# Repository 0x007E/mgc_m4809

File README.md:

# `MGC_module` - ATmega4809

The `ATmega4809` (`mgc_module`) is an adaptable board for the [MeGARCard](https://github.com/0x007e/mgc). The board offers the possibility to control the `MeGARCard` with an [ATmega4809](#additional-information). The board itself is connected to the `MeGARCard` within the pcb-to-pcb connectors (no soldering necessary). With the onboard dip-switches the board voltage can be regulated from `3V3` to `5V`. Also the usage of hardware-/software-`twi` to control the [SSD1306](#additional-information)-display on the megacard can be selected.

> To mount the board on the `MeGARCard` disconnect the power source (`USB-C` connector) or any other used source from the MeGARCard!

| Experience  | Level                                                                               |
|:------------|:-----------------------------------------------------------------------------------:|
| Soldering   |  |

# Downloads

| Type      | File                                                                                                                                                 | Description     |
|:---------:|:----------------------------------------------------------------------------------------------------------------------------------------------------:|:----------------|
| Schematic | [pdf](https://github.com/0x007E/mgc_m4809/releases/latest/download/schematic.pdf) / [cadlab](https://cadlab.io/project/30419/main/files)                   | Schematic files |
| Board     | [pdf](https://github.com/0x007E/mgc_m4809/releases/latest/download/pcb.pdf) / [cadlab](https://cadlab.io/project/30419/main/files)                         | Board file      |
| Drill     | [pdf](https://github.com/0x007E/mgc_m4809/releases/latest/download/drill.pdf)                                                                              | Drill file      |
| BoM | [xlsx](https://github.com/0x007E/mgc_m4809/releases/latest/download/bom.xlsx) / [html](https://github.com/0x007E/mgc_m4809/releases/latest/download/ibom.html)          | Bill of Material as Excel/interactive HTML |
| PCB    | [zip](https://github.com/0x007E/mgc_m4809/releases/latest/download/kicad.zip) / [tar](https://github.com/0x007E/mgc_m4809/releases/latest/download/kicad.tar.gz)    | KiCAD/Gerber/BoM/Drill files       |

# Hardware

The pcb is created with `KiCAD`. All files are built with `github actions` so that they are ready for a production environment.

## PCB

The circuit board is populated on both sides (Top, Bottom). The best way for soldering the `SMD` components is within a vapor phase soldering system and for the `THT` components with a standard soldering system.

### Top Layer

### Bottom Layer

# Additional Information

| Type       | Link               | Description              |
|:----------:|:------------------:|:-------------------------|
| ATmega4809  | [pdf](https://ww1.microchip.com/downloads/en/DeviceDoc/ATmega4808-4809-Data-Sheet-DS40002173A.pdf) | ATmega4808/4809 Data Sheet |
| SSD1306 | [pdf](https://www.vishay.com/docs/37902/oled128o064dbpp3n00000.pdf) | 128 x 64 Graphic OLED |

---

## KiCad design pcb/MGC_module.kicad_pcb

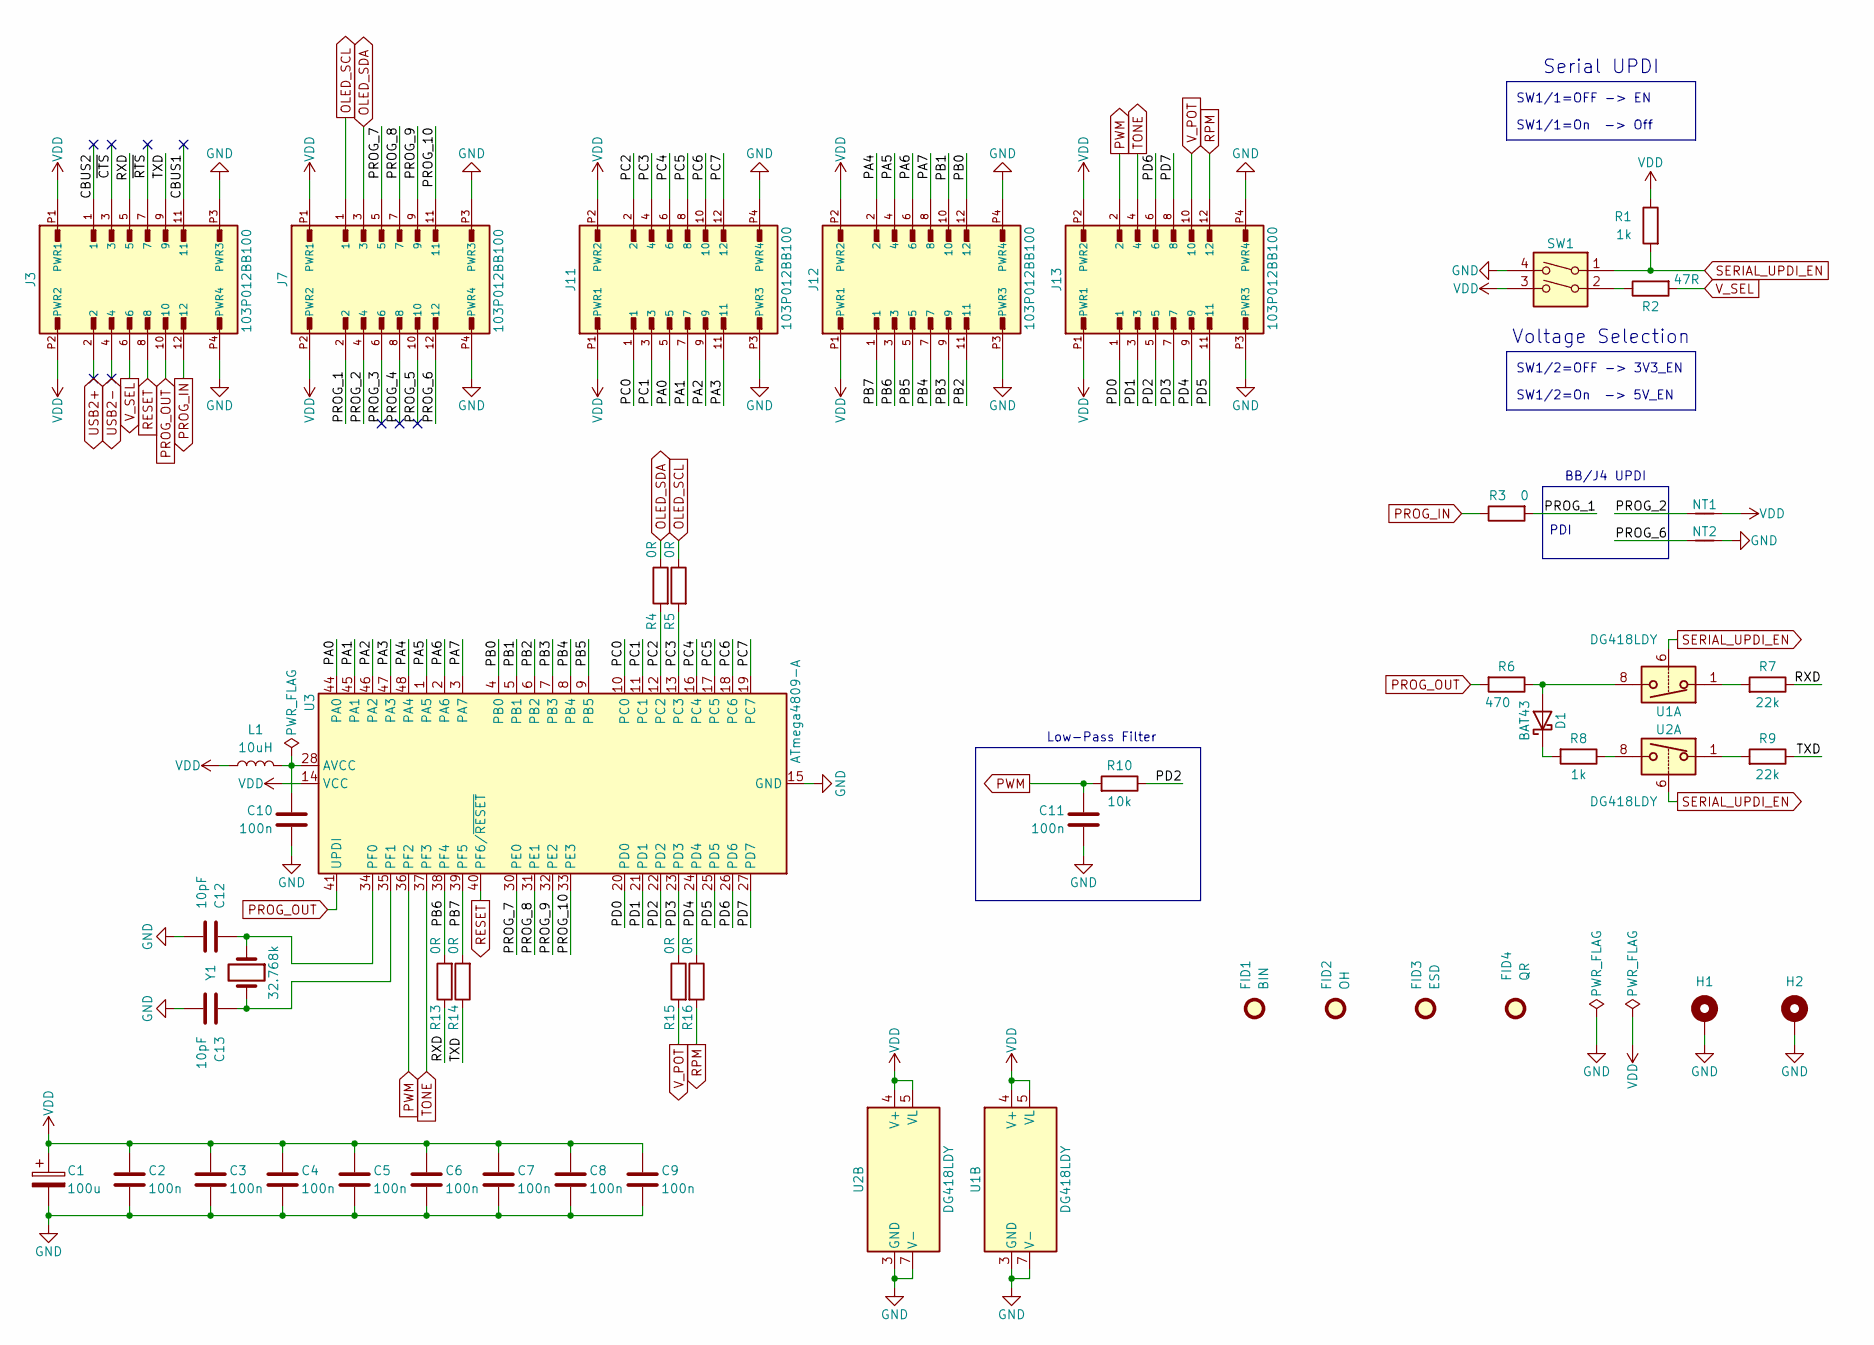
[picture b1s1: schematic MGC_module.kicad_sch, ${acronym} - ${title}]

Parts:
C1: 100u; CP_EIA-3528-21_Kemet-B; DigiKey 478-3877-1-ND
C2, C3, C4, C5, C6, C7, C8, C9, C10, C11: 100n; C_1206_3216Metric
C12, C13: 10pF; C_0603_1608Metric
D1: BAT43; D_MiniMELF
FID1: BIN; WEEE-Logo_4.2x6mm_SilkScreen
FID2: OH; OSHW-Logo2_7.3x6mm_SilkScreen
FID3: ESD; ESD-Logo_6.6x6mm_SilkScreen
FID4: QR; QR_0x007e_very_small
H1, H2: MountingHole_Pad; MountingHole_2.7mm_M2.5_DIN965_Pad
J3, J7, J11, J12, J13: 103P012BB100; AMPHENOL_103P012BB100; DigiKey 609-103P012BB100CT-ND
L1: 10uH; L_1206_3216Metric
NT1, NT2: NetTie_2; NetTie-2_SMD_Pad0.5mm
R1, R8: 1k; R_1206_3216Metric
R2: 47R; R_1206_3216Metric
R3: 0; R_1206_3216Metric
R4, R5, R13, R14, R15, R16: 0R; R_1206_3216Metric
R6: 470; R_1206_3216Metric
R7, R9: 22k; R_1206_3216Metric
R10: 10k; R_1206_3216Metric
SW1: SW_DIP_x02; SW_DIP_SPSTx02_Slide_6.7x6.64mm_W6.73mm_P2.54mm_LowProfile_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
U1, U2: DG418LDY; SOIC-8_3.9x4.9mm_P1.27mm; DigiKey DG417LEDY-T1-GE4CT-ND
U3: ATmega4809-A; TQFP-48_7x7mm_P0.5mm; DigiKey 150-ATMEGA4809-AURCT-ND
Y1: 32.768k; Crystal_SMD_3215-2Pin_3.2x1.5mm

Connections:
/CBUS1: J3.11
/CBUS2: J3.1
/PA0: J11.5, U3.44 (PA0)
/PA1: J11.7, U3.45 (PA1)
/PA2: J11.9, U3.46 (PA2)
/PA3: J11.11, U3.47 (PA3)
/PA4: J12.2, U3.48 (PA4)
/PA5: J12.4, U3.1 (PA5)
/PA6: J12.6, U3.2 (PA6)
/PA7: J12.8, U3.3 (PA7)
/PB0: J12.12, U3.4 (PB0)
/PB1: J12.10, U3.5 (PB1)
/PB2: J12.11, U3.6 (PB2)
/PB3: J12.9, U3.7 (PB3)
/PB4: J12.7, U3.8 (PB4)
/PB5: J12.5, U3.9 (PB5)
/PB6: J12.3, R13.2, U3.38 (PF4)
/PB7: J12.1, R14.2, U3.39 (PF5)
/PC0: J11.1, U3.10 (PC0)
/PC1: J11.3, U3.11 (PC1)
/PC2: J11.2, R4.2, U3.12 (PC2)
/PC3: J11.4, R5.2, U3.13 (PC3)
/PC4: J11.6, U3.16 (PC4)
/PC5: J11.8, U3.17 (PC5)
/PC6: J11.10, U3.18 (PC6)
/PC7: J11.12, U3.19 (PC7)
/PD0: J13.1, U3.20 (PD0)
/PD1: J13.3, U3.21 (PD1)
/PD2: J13.5, R10.1, U3.22 (PD2)
/PD3: J13.7, R15.1, U3.23 (PD3)
/PD4: J13.9, R16.1, U3.24 (PD4)
/PD5: J13.11, U3.25 (PD5)
/PD6: J13.6, U3.26 (PD6)
/PD7: J13.8, U3.27 (PD7)
/PROG_1: J7.2, R3.2
/PROG_2: J7.4, NT1.1
/PROG_3: J7.6
/PROG_4: J7.8
/PROG_5: J7.10
/PROG_6: J7.12, NT2.1
/PROG_7: J7.5, U3.30 (PE0)
/PROG_8: J7.7, U3.31 (PE1)
/PROG_9: J7.9, U3.32 (PE2)
/PROG_10: J7.11, U3.33 (PE3)
/RXD: J3.5, R7.1, R13.1
/TXD: J3.9, R9.1, R14.1
/~CTS: J3.3
/~RTS: J3.7
GND: C1.2, C2.2, C3.2, C4.2, C5.2, C6.2, C7.2, C8.2, C9.2, C10.2, C11.2, C12.2, C13.2, H1.1, H2.1, J3.P3 (PWR3), J3.P4 (PWR4), J7.P3 (PWR3), J7.P4 (PWR4), J11.P3 (PWR3), J11.P4 (PWR4), J12.P3 (PWR3), J12.P4 (PWR4), J13.P3 (PWR3), J13.P4 (PWR4), NT2.2, SW1.4, U1.3 (GND), U1.7 (V-), U2.3 (GND), U2.7 (V-), U3.15 (GND), U3.29 (GND), U3.43 (GND)
unnamed: D1.2 (A), R6.1, U1.8
unnamed: D1.1 (K), R8.2
unnamed: R2.1, SW1.2
unnamed: R7.2, U1.1
unnamed: R8.1, U2.8
unnamed: R9.2, U2.1
unnamed: C10.1, L1.2, U3.28 (AVCC)
unnamed: C12.1, U3.34 (PF0), Y1.1
unnamed: C13.1, U3.35 (PF1), Y1.2
OLED_SCL: J7.1, R5.1
OLED_SDA: J7.3, R4.1
PROG_IN: J3.12, R3.1
PROG_OUT: J3.10, R6.2, U3.41 (UPDI)
PWM: C11.1, J13.2, R10.2, U3.36 (PF2)
RESET: J3.8, U3.40 (PF6/~RESET)
RPM: J13.12, R16.2
SERIAL_UPDI_EN: R1.2, SW1.1, U1.6, U2.6
TONE: J13.4, U3.37 (PF3)
USB2+: J3.2
USB2-: J3.4
VDD: C1.1, C2.1, C3.1, C4.1, C5.1, C6.1, C7.1, C8.1, C9.1, J3.P1 (PWR1), J3.P2 (PWR2), J7.P1 (PWR1), J7.P2 (PWR2), J11.P1 (PWR1), J11.P2 (PWR2), J12.P1 (PWR1), J12.P2 (PWR2), J13.P1 (PWR1), J13.P2 (PWR2), L1.1, NT1.2, R1.1, SW1.3, U1.4 (V+), U1.5 (VL), U2.4 (V+), U2.5 (VL), U3.14 (VCC), U3.42 (VCC)
V_POT: J13.10, R15.2
V_SEL: J3.6, R2.2

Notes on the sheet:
SW1/2=OFF -> 3V3_EN
SW1/1=OFF -> EN
SW1/2=On -> 5V_EN
SW1/1=On -> Off
Low-Pass Filter
Voltage Selection
PDI
BB/J4 UPDI
Serial UPDI

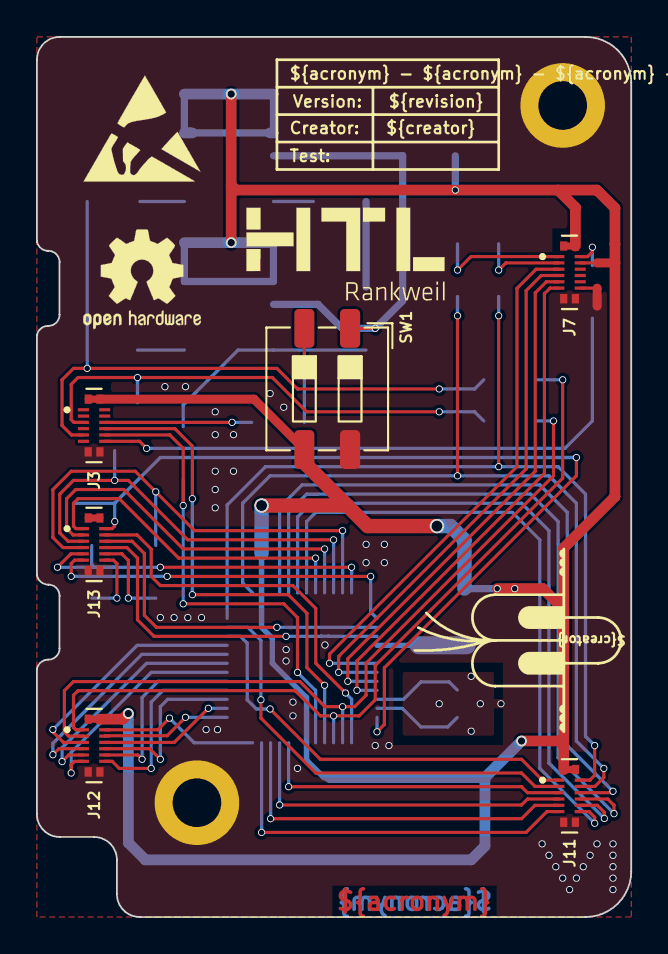
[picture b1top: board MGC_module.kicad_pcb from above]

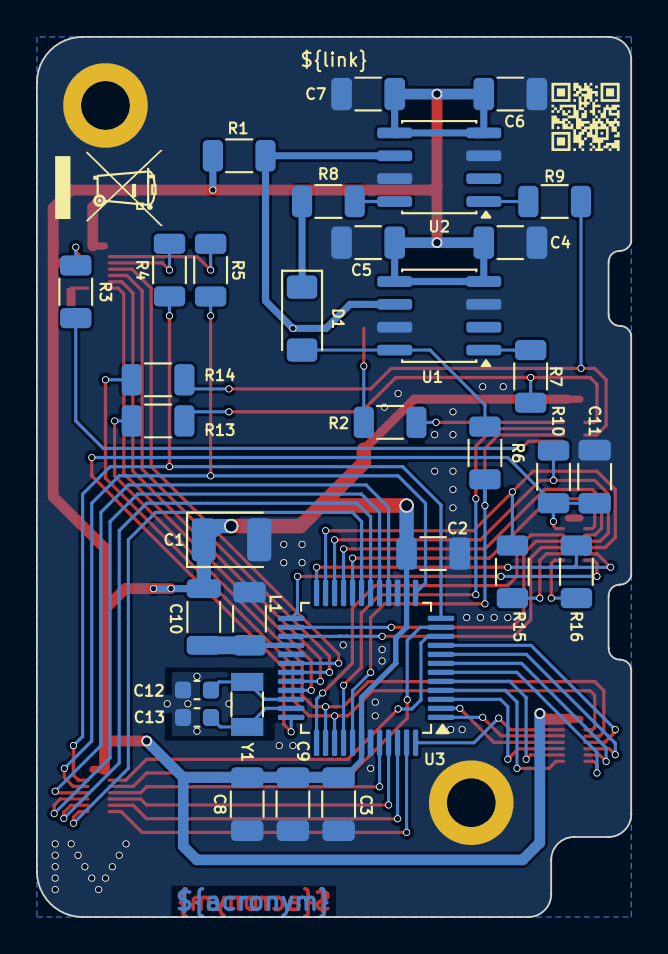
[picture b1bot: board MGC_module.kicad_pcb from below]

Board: 2 copper layers, 33.0 x 48.9 mm, 47 parts (35 on the bottom side), 63 nets.

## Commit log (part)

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2026-06-12 Add pcb layout
2026-06-12 Decrease font size of cu acronym
2026-06-18 Fix unconnected labels
2026-06-18 Add README.md
2026-06-18 Add build pipeline
2026-06-18 Add release pipeline
2026-06-23 Adapt output filenames
2026-06-23 Add missing values in bom
2026-06-23 Adapt config and update action versions

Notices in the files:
README.md:
License CC By-NC-SA
parts and their libraries:
license: CC BY-NC-SA 4.0
